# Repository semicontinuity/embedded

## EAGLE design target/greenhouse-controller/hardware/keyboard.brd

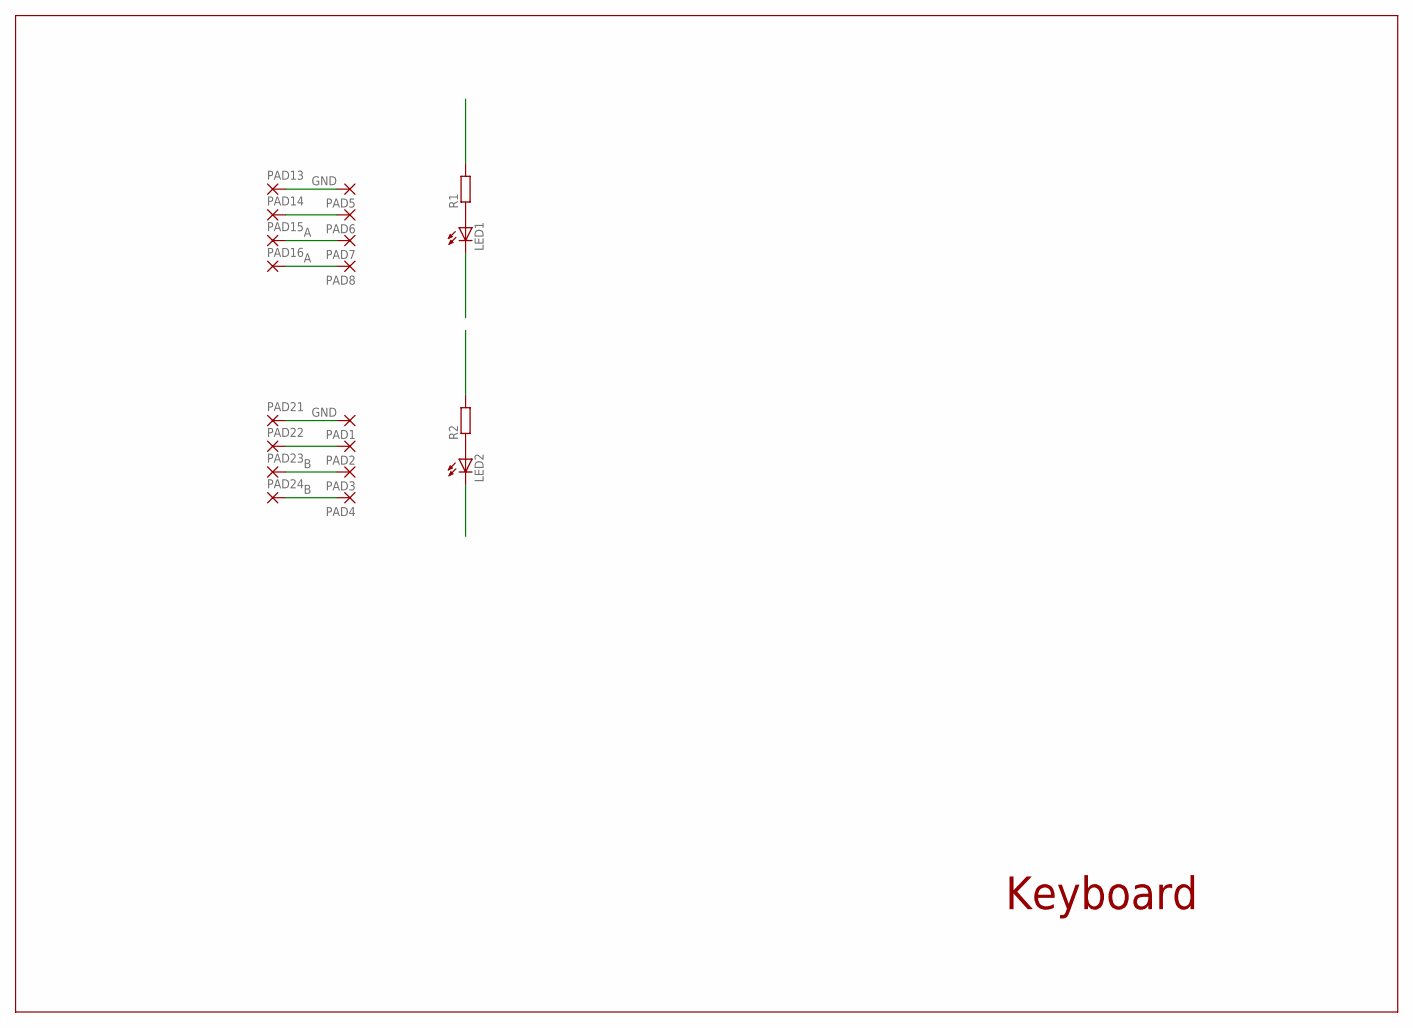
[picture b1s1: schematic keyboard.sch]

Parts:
LED1, LED2: LEDCHIP-LED0805; CHIP-LED0805
PAD1, PAD2, PAD3, PAD4, PAD5, PAD6, PAD7, PAD8, PAD13, PAD14, PAD15, PAD16, PAD21, PAD22, PAD23, PAD24: WIREPAD1,6/0,8; 1,6/0,8
R1, R2: R-EU_R0805; R0805

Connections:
A: PAD7.1, PAD8.1, PAD15.1, PAD16.1, R1.2
B: PAD3.1, PAD4.1, PAD23.1, PAD24.1, R2.2
GND: LED1.C, LED2.C, PAD1.1, PAD2.1, PAD5.1, PAD6.1, PAD13.1, PAD14.1, PAD21.1, PAD22.1
unnamed: LED1.A, R1.1
unnamed: LED2.A, R2.1

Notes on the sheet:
Keyboard

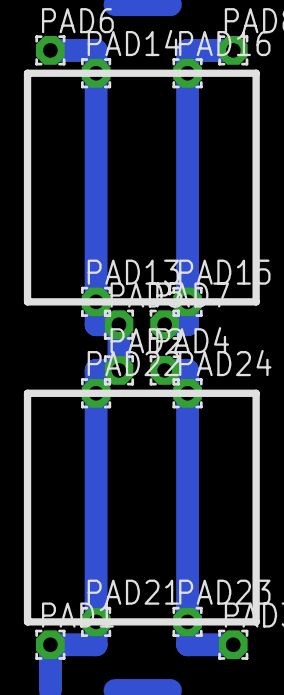
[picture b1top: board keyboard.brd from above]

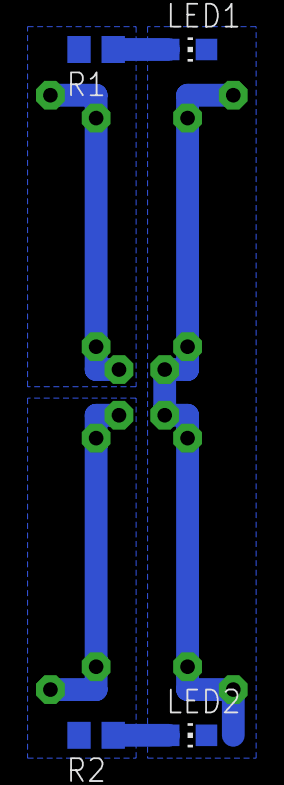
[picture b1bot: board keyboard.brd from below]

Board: 2 copper layers, 20 parts (4 on the bottom side), 5 nets.

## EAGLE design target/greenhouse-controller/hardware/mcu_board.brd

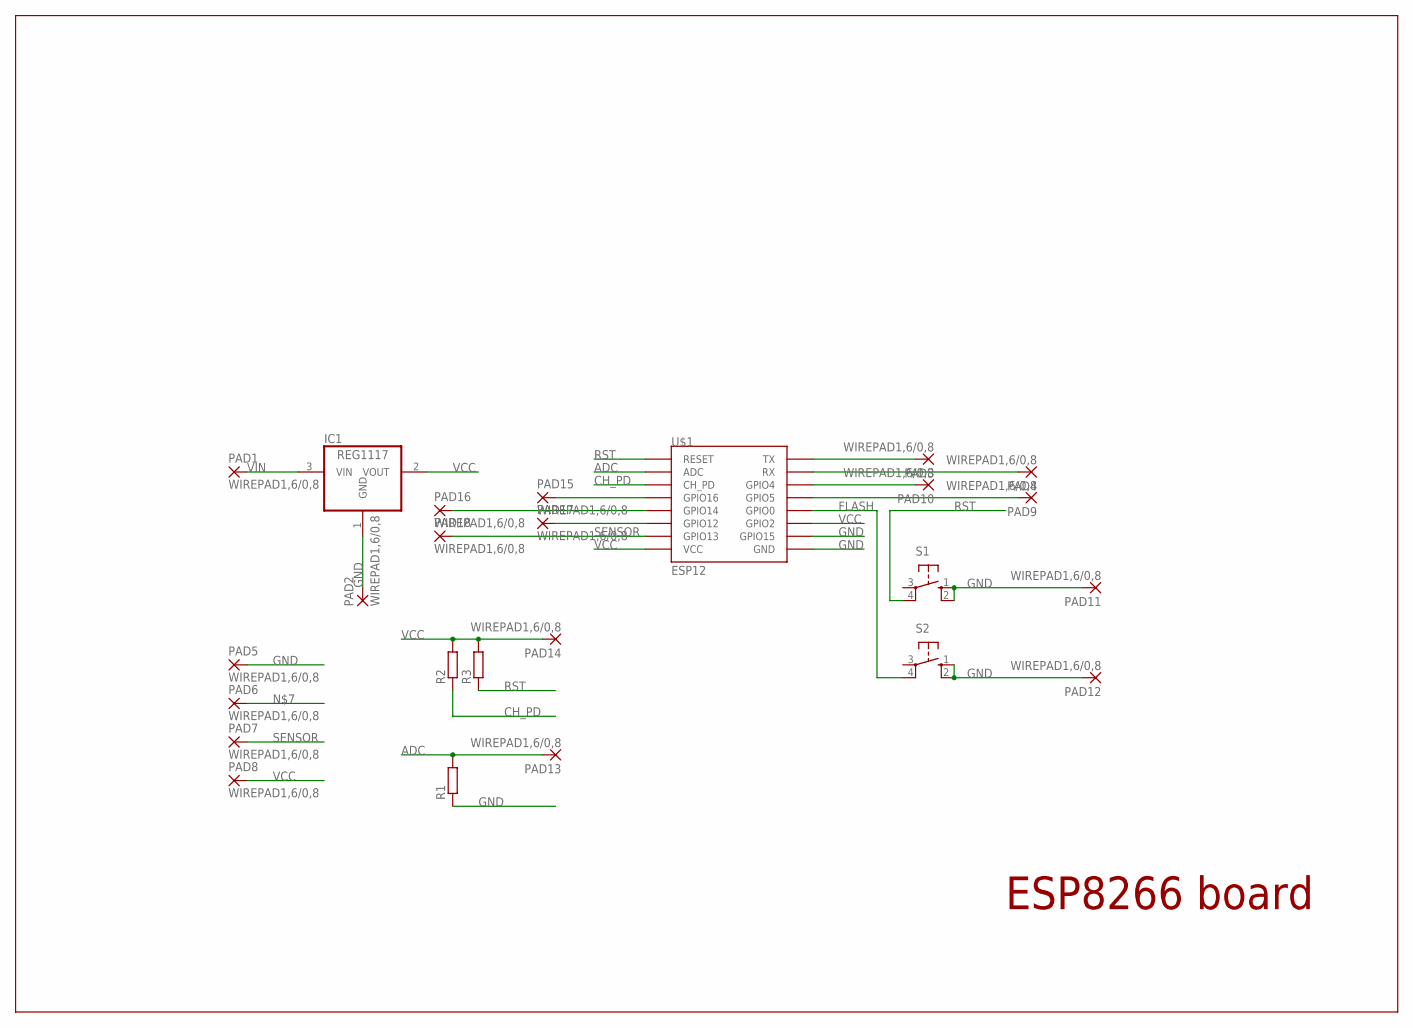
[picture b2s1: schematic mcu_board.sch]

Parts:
IC1: REG1117; SOT223
PAD1, PAD2, PAD3, PAD4, PAD5, PAD6, PAD7, PAD8, PAD9, PAD10, PAD11, PAD12, PAD13, PAD14, PAD15, PAD16, PAD17, PAD18: WIREPAD1,6/0,8; 1,6/0,8
R1, R2, R3: R-EU_M0805; M0805
S1, S2: 10-XX; B3F-10XX
U$1: ESP12

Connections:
ADC: PAD13.1, R1.2, U$1.ADC
CH_PD: R2.1, U$1.CH_PD
FLASH: S2.4 (P1), U$1.GPIO0
GND: IC1.1 (GND), PAD2.1, PAD5.1, PAD11.1, PAD12.1, R1.1, S1.1 (S), S1.2 (S1), S2.1 (S), S2.2 (S1), U$1.GND, U$1.GPIO15
unnamed: PAD3.1, U$1.TX
unnamed: PAD4.1, U$1.RX
unnamed: PAD10.1, U$1.GPIO4
unnamed: PAD9.1, U$1.GPIO5
unnamed: PAD15.1, U$1.GPIO16
unnamed: PAD16.1, U$1.GPIO14
unnamed: PAD17.1, U$1.GPIO12
RST: R3.1, S1.4 (P1), U$1.RESET
SENSOR: PAD7.1, PAD18.1, U$1.GPIO13
VCC: IC1.2 (VOUT), PAD8.1, PAD14.1, R2.2, R3.2, U$1.GPIO2, U$1.VCC
VIN: IC1.3 (VIN), PAD1.1

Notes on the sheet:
ESP8266 board

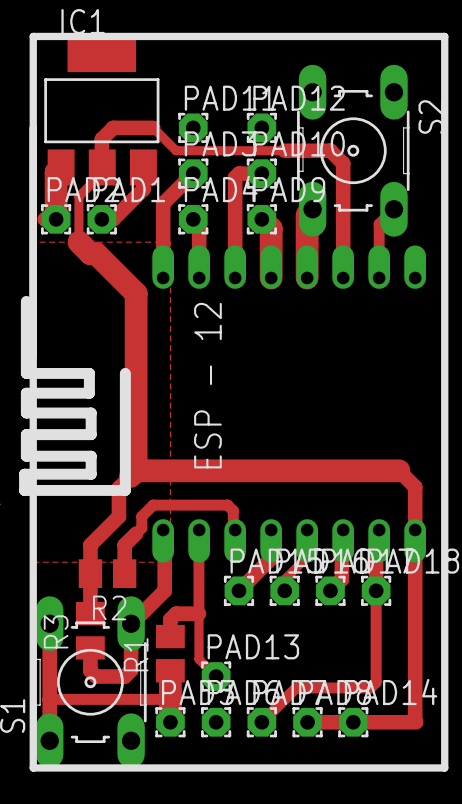
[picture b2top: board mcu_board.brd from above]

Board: 2 copper layers, 25 parts (0 on the bottom side), 15 nets.

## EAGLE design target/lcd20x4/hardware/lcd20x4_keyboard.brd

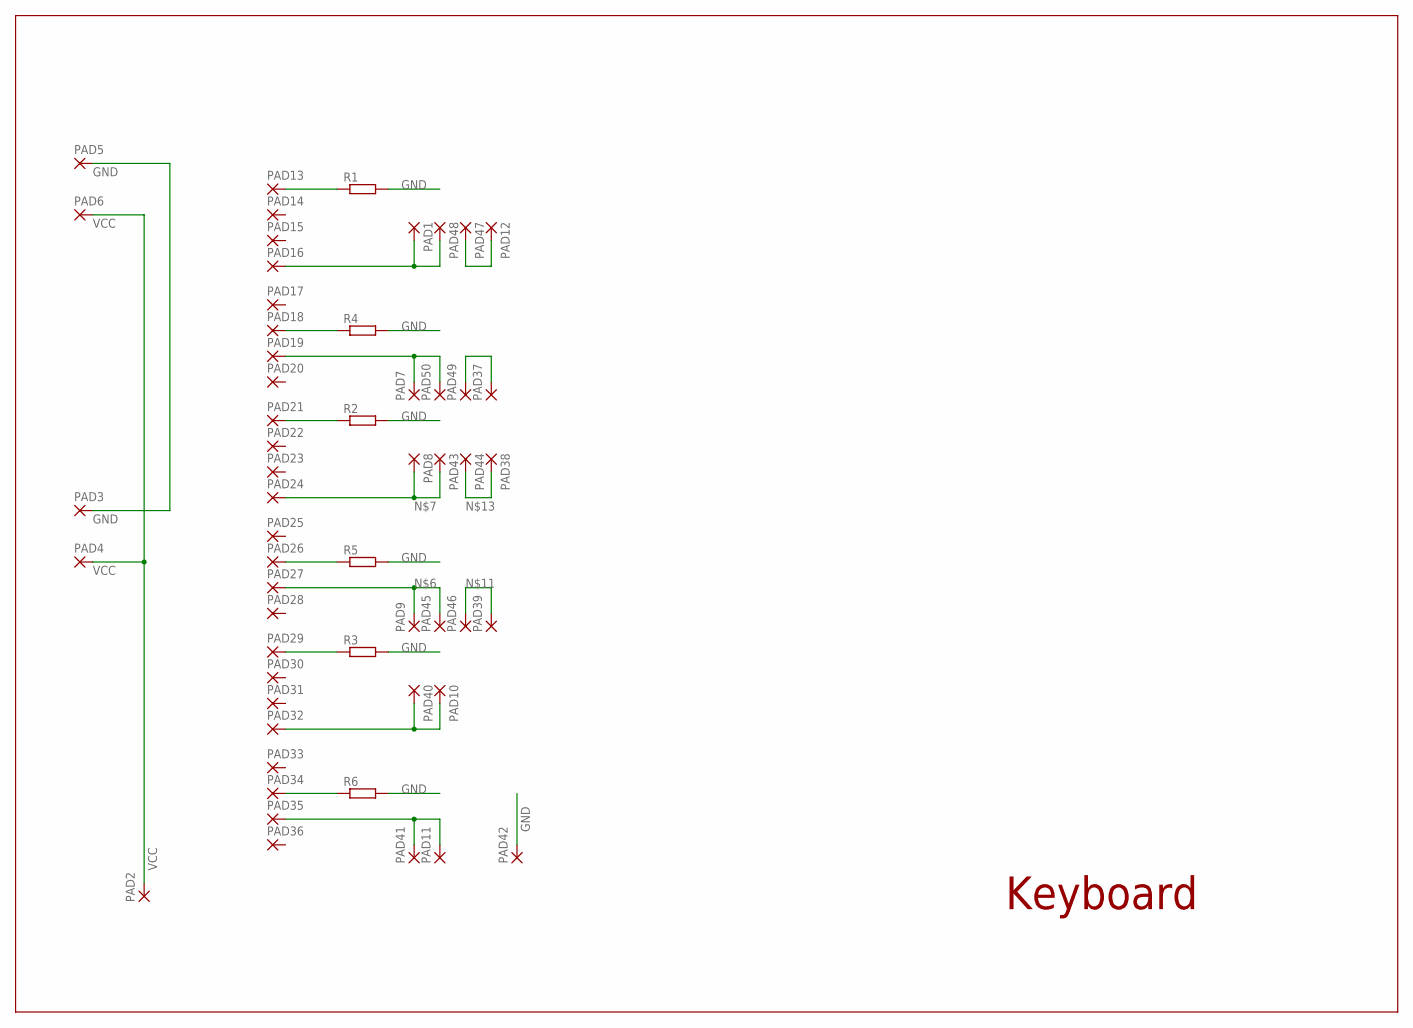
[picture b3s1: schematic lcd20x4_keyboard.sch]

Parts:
PAD1, PAD2, PAD3, PAD4, PAD5, PAD6, PAD7, PAD8, PAD9, PAD10, PAD11, PAD12, PAD13, PAD14, PAD15, PAD16, PAD17, PAD18, PAD19, PAD20, PAD21, PAD22, PAD23, PAD24, PAD25, PAD26, PAD27, PAD28, PAD29, PAD30, PAD31, PAD32, PAD33, PAD34, PAD35, PAD36, PAD37, PAD38, PAD39, PAD40, PAD41, PAD42, PAD43, PAD44, PAD45, PAD46, PAD47, PAD48, PAD49, PAD50: WIREPAD1,6/0,8; 1,6/0,8
R1, R2, R3, R4, R5, R6: R-EU_M0805; M0805

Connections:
GND: PAD3.1, PAD5.1, PAD42.1, R1.2, R2.2, R3.2, R4.2, R5.2, R6.2
unnamed: PAD29.1, R3.1
unnamed: PAD21.1, R2.1
unnamed: PAD13.1, R1.1
unnamed: PAD10.1, PAD32.1, PAD40.1
unnamed: PAD11.1, PAD35.1, PAD41.1
unnamed: PAD9.1, PAD27.1, PAD45.1
unnamed: PAD8.1, PAD24.1, PAD43.1
unnamed: PAD1.1, PAD16.1, PAD48.1
unnamed: PAD7.1, PAD19.1, PAD50.1
unnamed: PAD34.1, R6.1
unnamed: PAD39.1, PAD46.1
unnamed: PAD26.1, R5.1
unnamed: PAD38.1, PAD44.1
unnamed: PAD18.1, R4.1
unnamed: PAD37.1, PAD49.1
unnamed: PAD12.1, PAD47.1
VCC: PAD2.1, PAD4.1, PAD6.1

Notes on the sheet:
Keyboard

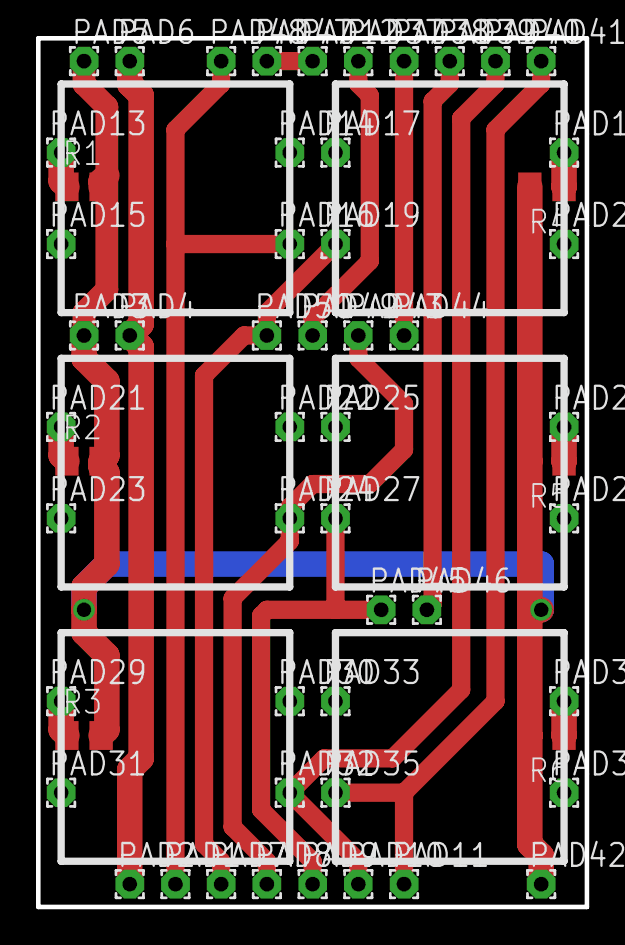
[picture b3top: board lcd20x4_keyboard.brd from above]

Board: 2 copper layers, 30.5 x 48.3 mm, 56 parts (0 on the bottom side), 18 nets.

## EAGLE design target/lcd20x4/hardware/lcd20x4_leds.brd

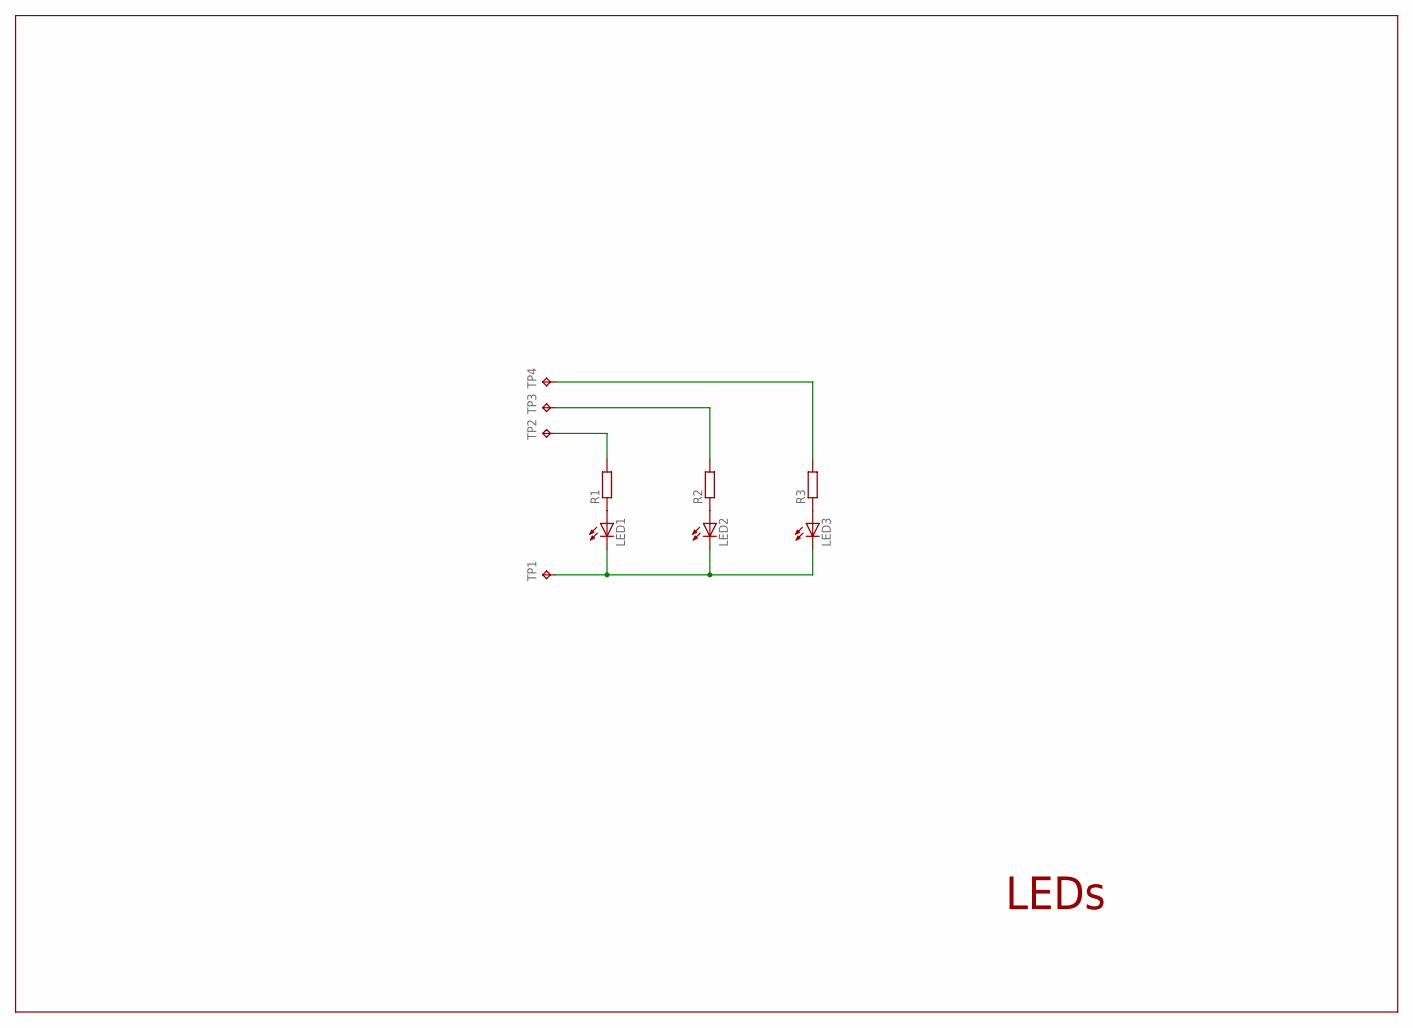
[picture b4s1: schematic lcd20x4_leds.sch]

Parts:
LED1, LED2, LED3: LED5MM
R1, R2, R3: R-EU_R0805; R0805
TP1, TP2, TP3, TP4: TPB1,27; B1,27

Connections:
GND: LED1.K (C), LED2.K (C), LED3.K (C), TP1.TP
unnamed: LED1.A, R1.1
unnamed: LED2.A, R2.1
unnamed: LED3.A, R3.1
unnamed: R1.2, TP2.TP
unnamed: R2.2, TP3.TP
unnamed: R3.2, TP4.TP

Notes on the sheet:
LEDs

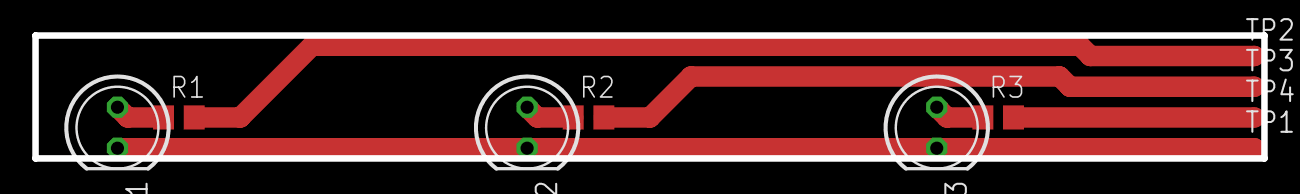
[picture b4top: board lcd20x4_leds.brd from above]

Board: 2 copper layers, 76.2 x 7.6 mm, 10 parts (0 on the bottom side), 7 nets.

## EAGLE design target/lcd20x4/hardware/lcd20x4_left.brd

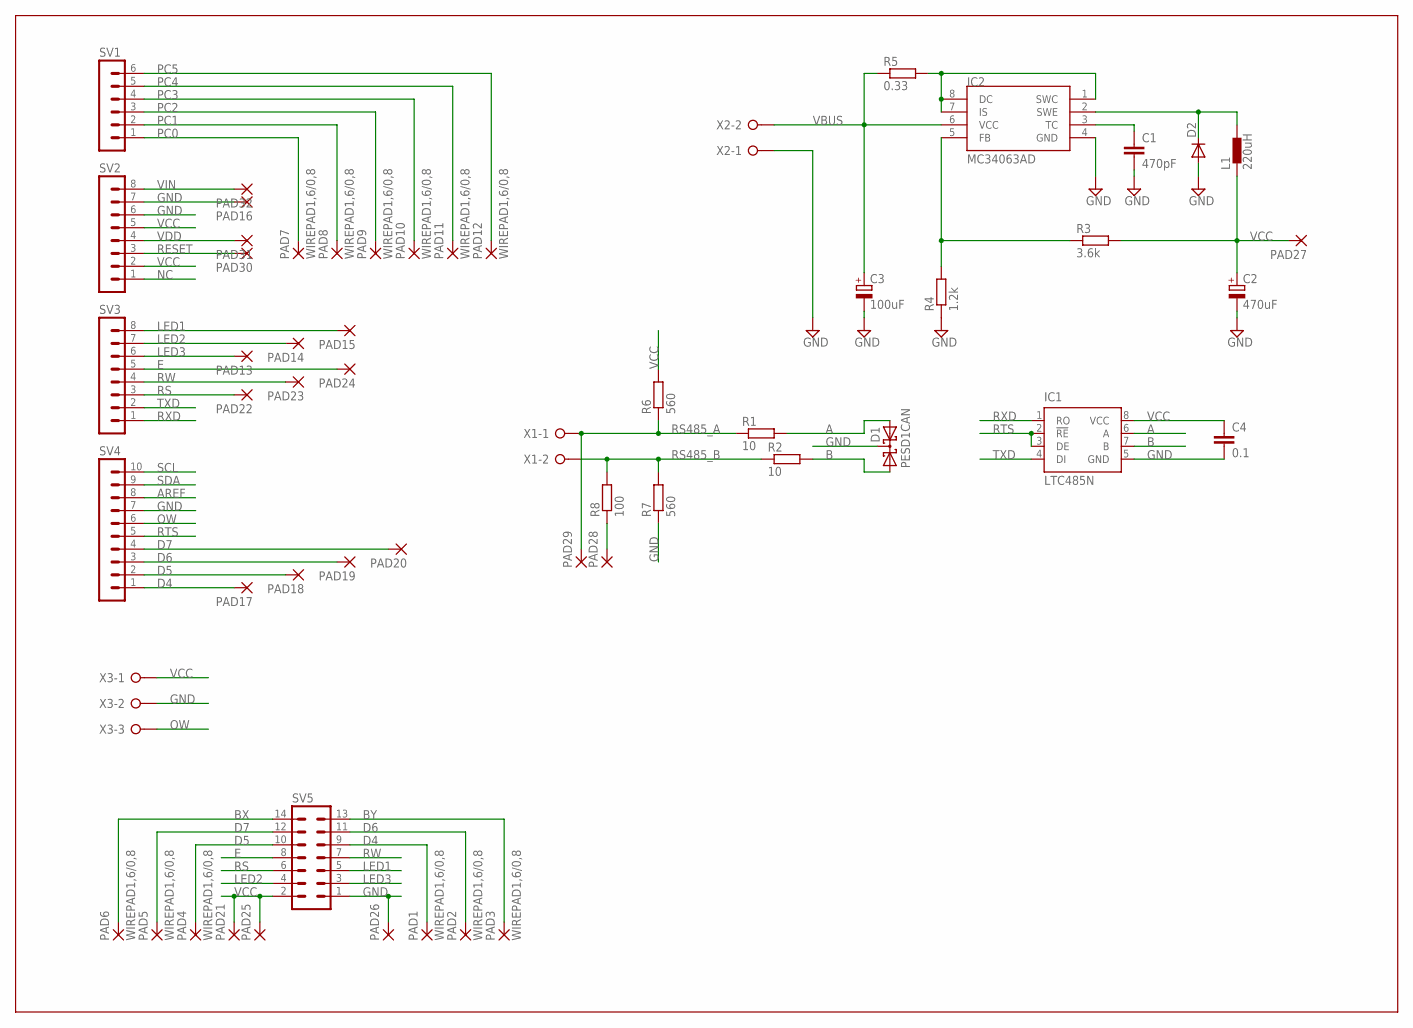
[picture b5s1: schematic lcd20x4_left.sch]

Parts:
C1: 470pF; C0805
C2: 470uF; E3,5-8
C3: 100uF; E3,5-8
C4: 0.1; C0805
D1: PESD1CAN; SOT23
D2: DIODE-SMB; SMB
IC1: LTC485N; DIL08
IC2: MC34063AD; SOIC8
L1: 220uH; DR1030
PAD1, PAD2, PAD3, PAD4, PAD5, PAD6, PAD7, PAD8, PAD9, PAD10, PAD11, PAD12, PAD13, PAD14, PAD15, PAD16, PAD17, PAD18, PAD19, PAD20, PAD21, PAD22, PAD23, PAD24, PAD25, PAD26, PAD27, PAD28, PAD29, PAD30, PAD31, PAD32: WIREPAD1,6/0,8; 1,6/0,8
R1, R2: 10; 0207/10
R3: 3.6k; R0805
R4: 1.2k; R0805
R5: 0.33; M1206
R6, R7: 560; 0207/10
R8: 100; 0207/10
SV1: MA06-1
SV2, SV3: MA08-1
SV4: MA10-1
SV5: MA07-2
X1, X2: W237-02P; W237-132
X3: W237-03P; W237-133

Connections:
A: D1.2 (A2), IC1.6 (A), R1.2
AREF: SV4.8
B: D1.1 (A1), IC1.7 (B), R2.2
BX: PAD6.1, SV5.14
BY: PAD3.1, SV5.13
D4: PAD1.1, PAD17.1, SV4.1, SV5.9
D5: PAD4.1, PAD18.1, SV4.2, SV5.10
D6: PAD2.1, PAD19.1, SV4.3, SV5.11
D7: PAD5.1, PAD20.1, SV4.4, SV5.12
E: PAD24.1, SV3.5, SV5.8
GND: C1.2, C2.-, C3.-, C4.2, D1.3 (CC), D2.A, IC1.5 (GND), IC2.4 (GND), PAD16.1, PAD26.1, R4.1, R7.1, SV2.6, SV2.7, SV4.7, SV5.1, X2.1, X3.2
LED1: PAD15.1, SV3.8, SV5.5
LED2: PAD14.1, SV3.7, SV5.4
LED3: PAD13.1, SV3.6, SV5.3
unnamed: C1.1, IC2.3 (TC)
unnamed: D2.C, IC2.2 (SWE), L1.2
unnamed: IC2.1 (SWC), IC2.7 (IS), IC2.8 (DC), R5.2
unnamed: IC2.5 (FB), R3.1, R4.2
unnamed: PAD28.1, R8.1
NC: SV2.1
OW: SV4.6, X3.3
PC0: PAD7.1, SV1.1
PC1: PAD8.1, SV1.2
PC2: PAD9.1, SV1.3
PC3: PAD10.1, SV1.4
PC4: PAD11.1, SV1.5
PC5: PAD12.1, SV1.6
RESET: PAD30.1, SV2.3
RS: PAD22.1, SV3.3, SV5.6
RS485_A: PAD29.1, R1.1, R6.1, X1.1
RS485_B: R2.1, R7.2, R8.2, X1.2
RTS: IC1.2 (!RE), IC1.3 (DE), SV4.5
RW: PAD23.1, SV3.4, SV5.7
RXD: IC1.1 (RO), SV3.1
SCL: SV4.10
SDA: SV4.9
TXD: IC1.4 (DI), SV3.2
VBUS: C3.+, IC2.6 (VCC), R5.1, X2.2
VCC: C2.+, C4.1, IC1.8 (VCC), L1.1, PAD21.1, PAD25.1, PAD27.1, R3.2, R6.2, SV2.2, SV2.5, SV5.2, X3.1
VDD: PAD31.1, SV2.4
VIN: PAD32.1, SV2.8

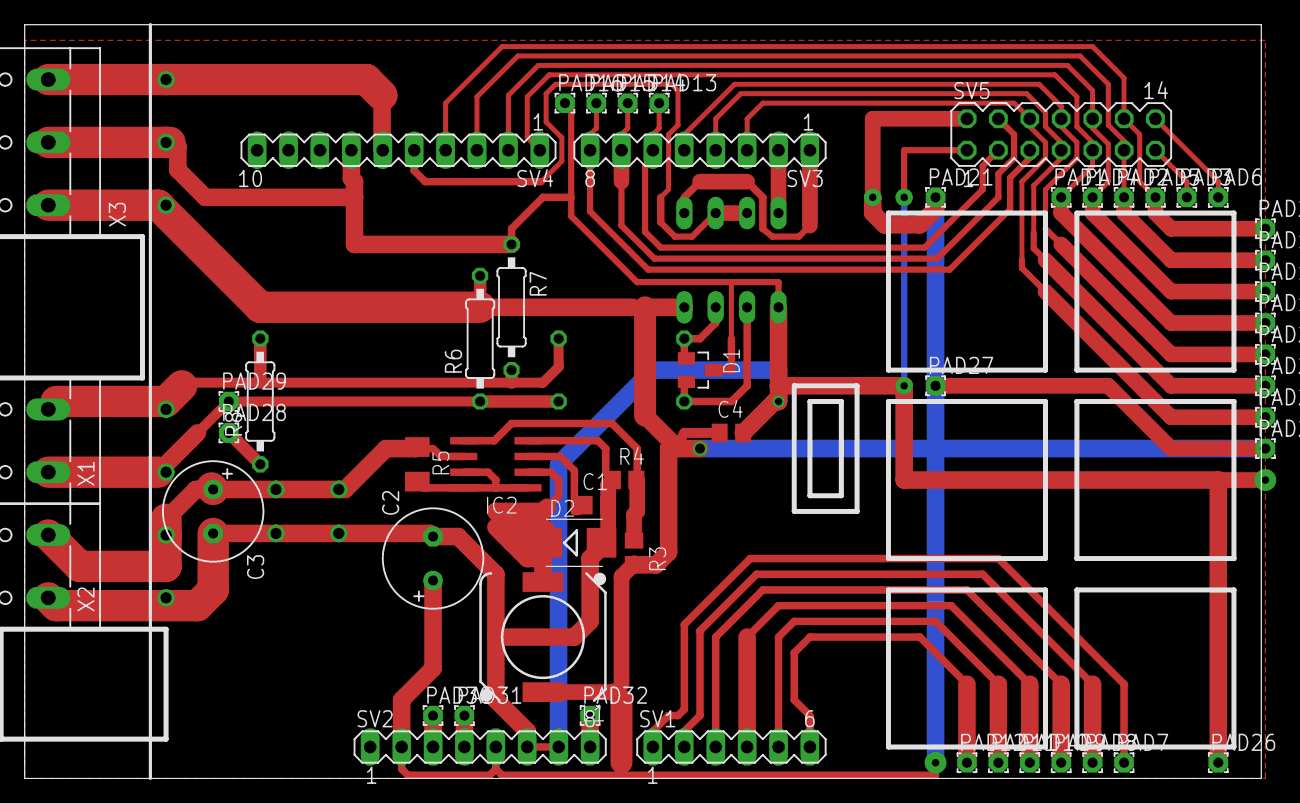
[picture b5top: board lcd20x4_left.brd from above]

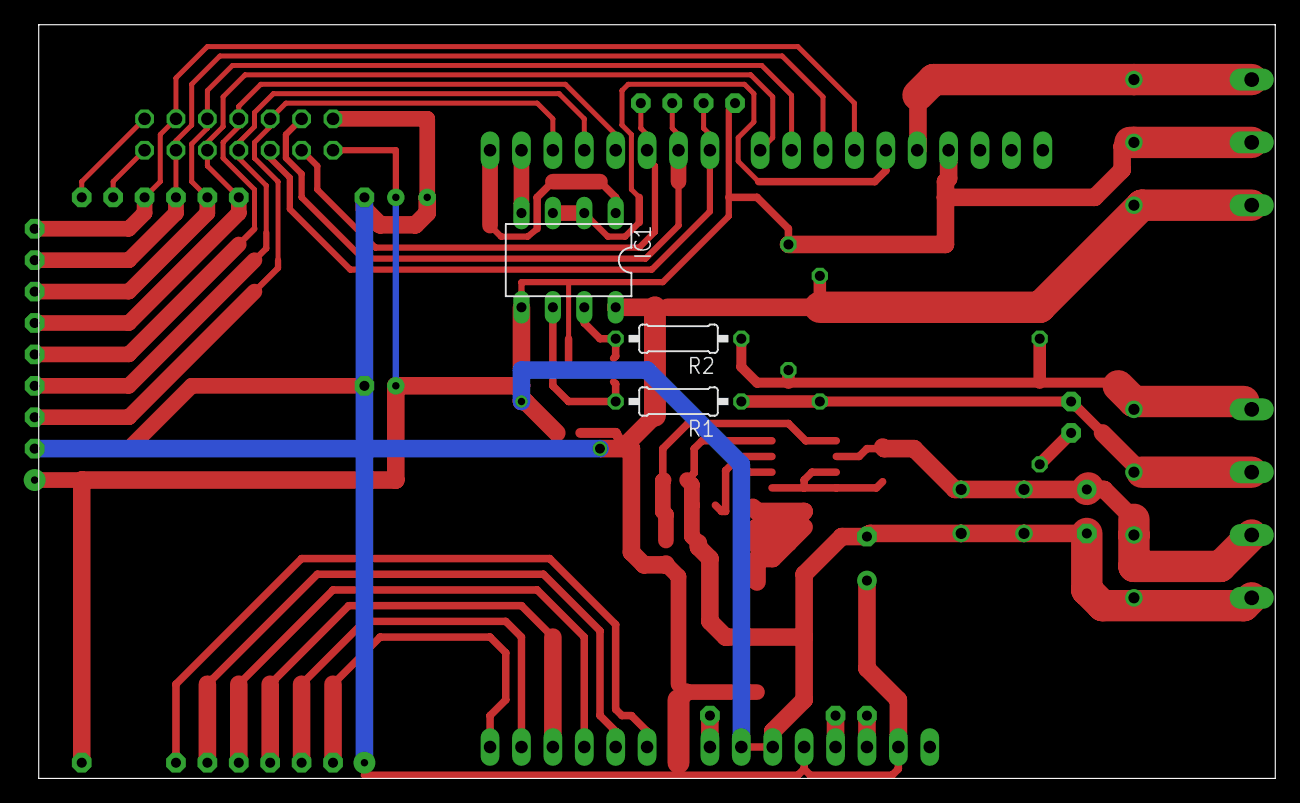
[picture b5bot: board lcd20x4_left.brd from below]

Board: 2 copper layers, 100.0 x 61.0 mm, 57 parts (3 on the bottom side), 37 nets.

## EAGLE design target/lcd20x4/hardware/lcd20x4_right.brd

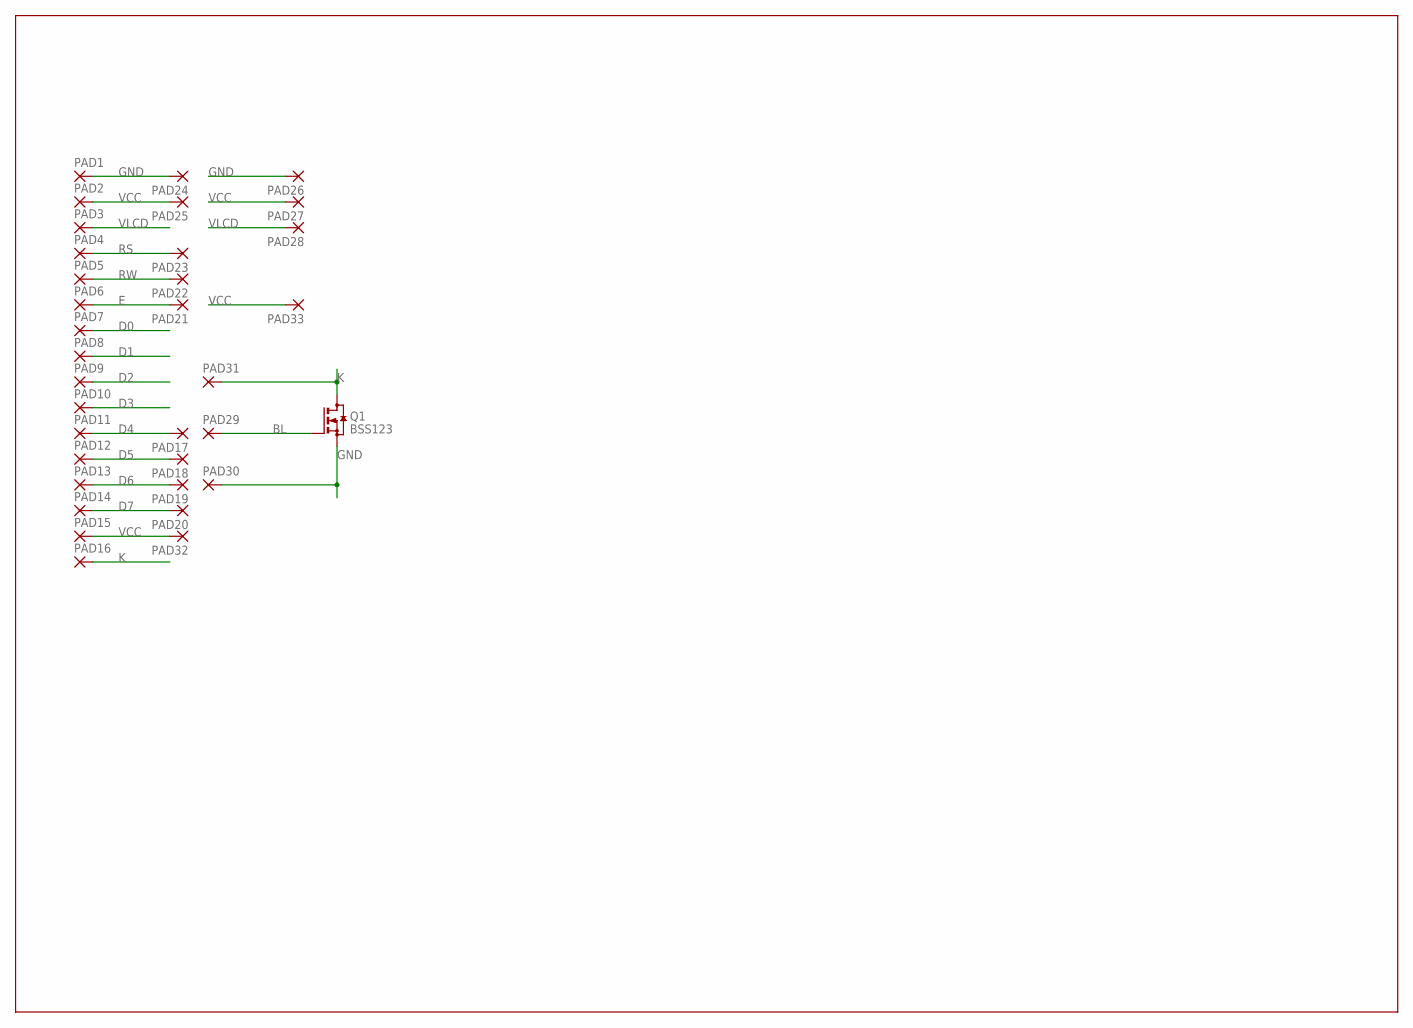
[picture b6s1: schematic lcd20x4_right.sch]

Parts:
PAD1, PAD2, PAD3, PAD4, PAD5, PAD6, PAD7, PAD8, PAD9, PAD10, PAD11, PAD12, PAD13, PAD14, PAD15, PAD16, PAD17, PAD18, PAD19, PAD20, PAD21, PAD22, PAD23, PAD24, PAD25, PAD26, PAD27, PAD28, PAD29, PAD30, PAD31, PAD32, PAD33: WIREPAD1,6/0,8; 1,6/0,8
Q1: BSS123; SOT23

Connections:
BL: PAD29.1, Q1.1 (G)
D0: PAD7.1
D1: PAD8.1
D2: PAD9.1
D3: PAD10.1
D4: PAD11.1, PAD17.1
D5: PAD12.1, PAD18.1
D6: PAD13.1, PAD19.1
D7: PAD14.1, PAD20.1
E: PAD6.1, PAD21.1
GND: PAD1.1, PAD24.1, PAD26.1, PAD30.1, Q1.2 (S)
K: PAD16.1, PAD31.1, Q1.3 (D)
RS: PAD4.1, PAD23.1
RW: PAD5.1, PAD22.1
VCC: PAD2.1, PAD15.1, PAD25.1, PAD27.1, PAD32.1, PAD33.1
VLCD: PAD3.1, PAD28.1

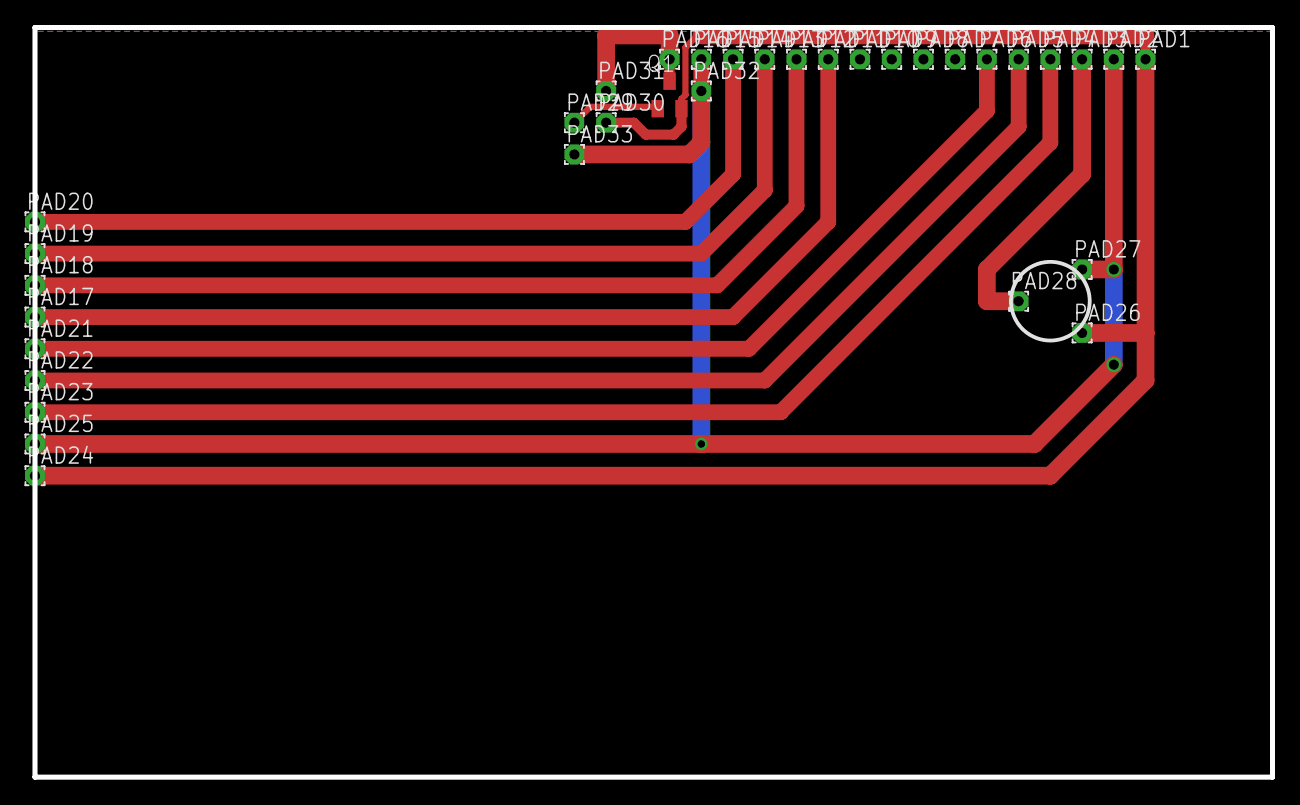
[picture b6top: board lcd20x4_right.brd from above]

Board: 2 copper layers, 99.1 x 60.0 mm, 34 parts (0 on the bottom side), 12 nets.

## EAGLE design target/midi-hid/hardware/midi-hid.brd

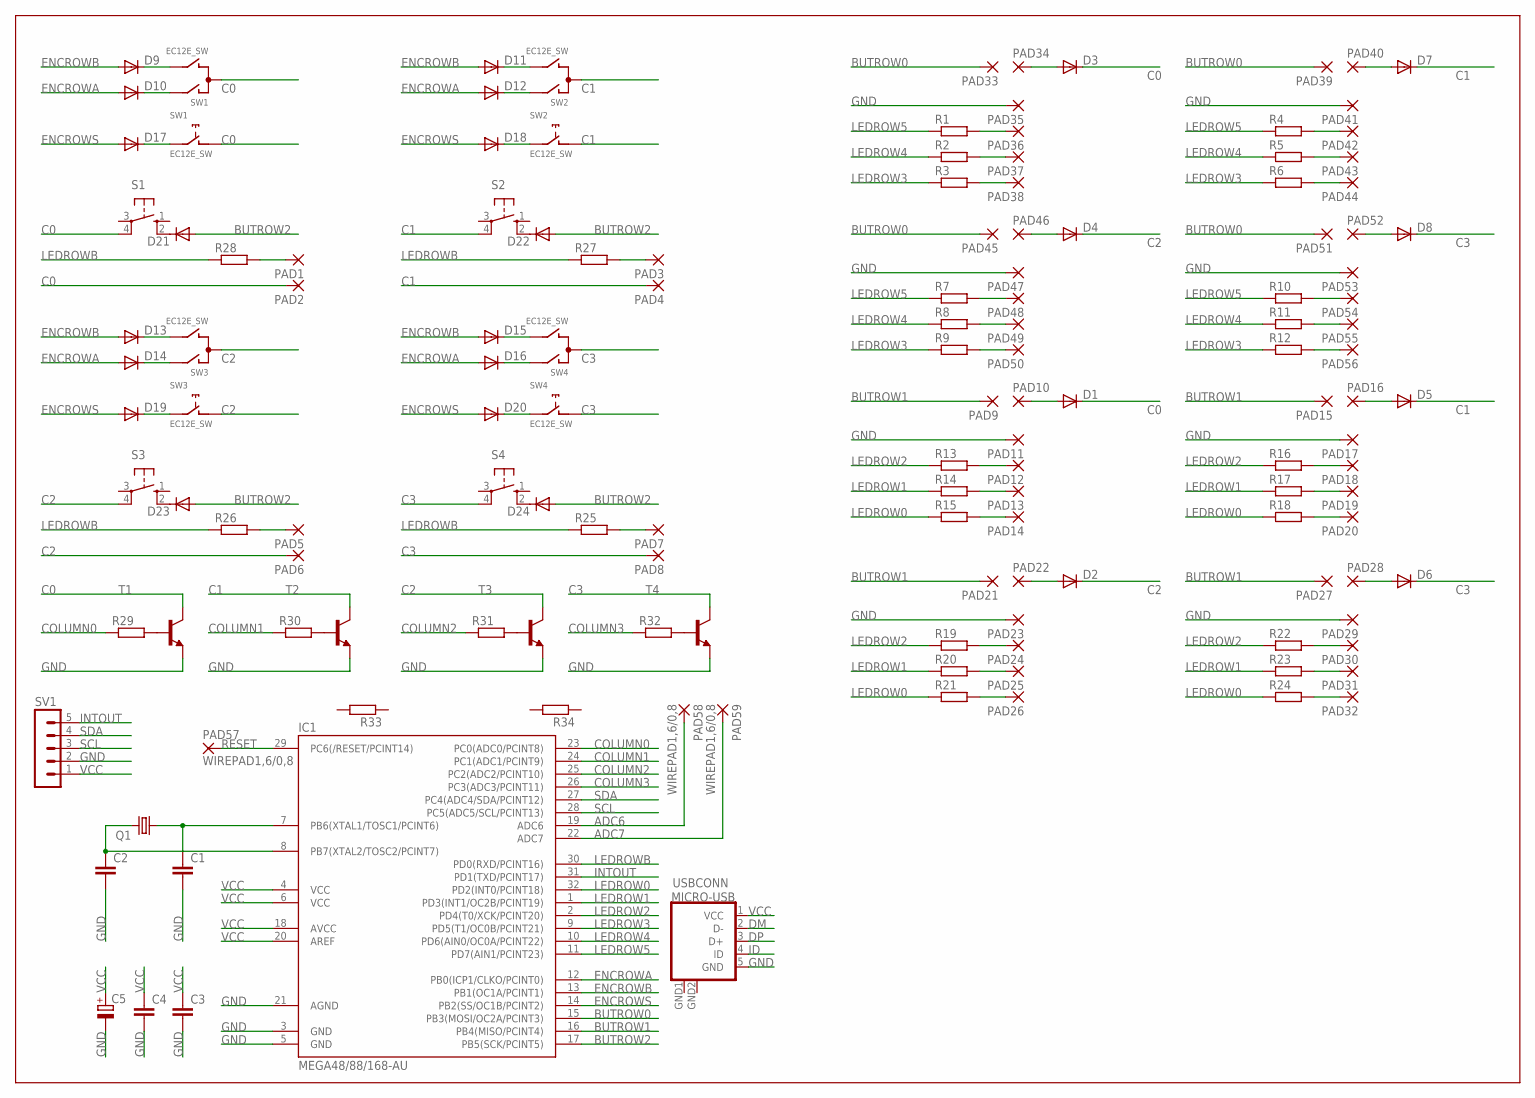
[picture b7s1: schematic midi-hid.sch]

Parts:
C1, C2, C3, C4: C-EUC0805; C0805
C5: CPOL-EUE2.5-6; E2,5-6
D1, D2, D3, D4, D5, D6, D7, D8, D9, D10, D11, D12, D13, D14, D15, D16, D17, D18, D19, D20, D21, D22, D23, D24: DIODE-SOD80C; SOD80C
IC1: MEGA48/88/168-AU; TQFP32-08
PAD1, PAD2, PAD3, PAD4, PAD5, PAD6, PAD7, PAD8, PAD9, PAD10, PAD11, PAD12, PAD13, PAD14, PAD15, PAD16, PAD17, PAD18, PAD19, PAD20, PAD21, PAD22, PAD23, PAD24, PAD25, PAD26, PAD27, PAD28, PAD29, PAD30, PAD31, PAD32, PAD33, PAD34, PAD35, PAD36, PAD37, PAD38, PAD39, PAD40, PAD41, PAD42, PAD43, PAD44, PAD45, PAD46, PAD47, PAD48, PAD49, PAD50, PAD51, PAD52, PAD53, PAD54, PAD55, PAD56: 1,6/0,8
PAD57, PAD58, PAD59: WIREPAD1,6/0,8; 1,6/0,8
Q1: CRYSTALHC49S; HC49/S
R1, R2, R3, R4, R5, R6, R7, R8, R9, R10, R11, R12, R13, R14, R15, R16, R17, R18, R19, R20, R21, R22, R23, R24, R25, R26, R27, R28, R29, R30, R31, R32: R-EU_R0805; R0805
R33, R34: R-EU_0207/10; 0207/10
S1, S2, S3, S4: 40-XX; B3F-40XX
SV1: MA05-1
SW1, SW2, SW3, SW4: EC12E_SW; ALPS_EC12E_SW
T1, T2, T3, T4: MMBT3904LT1-NPN-SOT23-BEC; SOT23-BEC
USBCONN: MICRO-USB

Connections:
ADC6: IC1.19 (ADC6), PAD58.1
ADC7: IC1.22 (ADC7), PAD59.1
BUTROW0: IC1.15 (PB3(MOSI/OC2A/PCINT3)), PAD33.1, PAD39.1, PAD45.1, PAD51.1
BUTROW1: IC1.16 (PB4(MISO/PCINT4)), PAD9.1, PAD15.1, PAD21.1, PAD27.1
BUTROW2: D21.A, D22.A, D23.A, D24.A, IC1.17 (PB5(SCK/PCINT5))
C0: D1.C, D3.C, PAD2.1, S1.4 (P1), SW1.C, SW1.D (1), T1.C
C1: D5.C, D7.C, PAD4.1, S2.4 (P1), SW2.C, SW2.D (1), T2.C
C2: D2.C, D4.C, PAD6.1, S3.4 (P1), SW3.C, SW3.D (1), T3.C
C3: D6.C, D8.C, PAD8.1, S4.4 (P1), SW4.C, SW4.D (1), T4.C
COLUMN0: IC1.23 (PC0(ADC0/PCINT8)), R29.1
COLUMN1: IC1.24 (PC1(ADC1/PCINT9)), R30.1
COLUMN2: IC1.25 (PC2(ADC2/PCINT10)), R31.1
COLUMN3: IC1.26 (PC3(ADC3/PCINT11)), R32.1
DM: USBCONN.2 (D-); also elsewhere on the board
DP: USBCONN.3 (D+); also elsewhere on the board
ENCROWA: D10.A, D12.A, D14.A, D16.A, IC1.12 (PB0(ICP1/CLKO/PCINT0))
ENCROWB: D9.A, D11.A, D13.A, D15.A, IC1.13 (PB1(OC1A/PCINT1))
ENCROWS: D17.A, D18.A, D19.A, D20.A, IC1.14 (PB2(SS/OC1B/PCINT2))
GND: C1.2, C2.2, C3.2, C4.2, C5.-, IC1.3 (GND), IC1.5 (GND), IC1.21 (AGND), PAD11.1, PAD17.1, PAD23.1, PAD29.1, PAD35.1, PAD41.1, PAD47.1, PAD53.1, SV1.2, T1.E, T2.E, T3.E, T4.E, USBCONN.5 (GND), USBCONN.GND1 (GND), USBCONN.GND2 (GND); also elsewhere on the board
ID: USBCONN.4 (ID)
INTOUT: IC1.31 (PD1(TXD/PCINT17)), SV1.5
LEDROW2: IC1.2 (PD4(T0/XCK/PCINT20)), R13.1, R16.1, R19.1, R22.1
LEDROW3: IC1.9 (PD5(T1/OC0B/PCINT21)), R3.1, R6.1, R9.1, R12.1
LEDROW4: IC1.10 (PD6(AIN0/OC0A/PCINT22)), R2.1, R5.1, R8.1, R11.1
LEDROW5: IC1.11 (PD7(AIN1/PCINT23)), R1.1, R4.1, R7.1, R10.1
LEDROWB: IC1.30 (PD0(RXD/PCINT16)), R25.1, R26.1, R27.1, R28.1
unnamed: D9.C, SW1.B
unnamed: D10.C, SW1.A
unnamed: D17.C, SW1.E (2)
unnamed: D11.C, SW2.B
unnamed: D12.C, SW2.A
unnamed: D18.C, SW2.E (2)
unnamed: D13.C, SW3.B
unnamed: D14.C, SW3.A
unnamed: D19.C, SW3.E (2)
unnamed: D15.C, SW4.B
unnamed: D16.C, SW4.A
unnamed: D20.C, SW4.E (2)
unnamed: C1.1, IC1.7 (PB6(XTAL1/TOSC1/PCINT6)), Q1.1
unnamed: C2.1, IC1.8 (PB7(XTAL2/TOSC2/PCINT7)), Q1.2
unnamed: R29.2, T1.B
unnamed: PAD36.1, R1.2
unnamed: PAD37.1, R2.2
unnamed: PAD38.1, R3.2
unnamed: R30.2, T2.B
unnamed: PAD42.1, R4.2
unnamed: PAD43.1, R5.2
unnamed: PAD44.1, R6.2
unnamed: R31.2, T3.B
unnamed: PAD48.1, R7.2
unnamed: PAD49.1, R8.2
unnamed: PAD50.1, R9.2
unnamed: R32.2, T4.B
unnamed: PAD54.1, R10.2
unnamed: PAD55.1, R11.2
unnamed: PAD56.1, R12.2
unnamed: D3.A, PAD34.1
unnamed: D7.A, PAD40.1
unnamed: D4.A, PAD46.1
unnamed: D8.A, PAD52.1
unnamed: PAD14.1, R15.2
unnamed: PAD13.1, R14.2
unnamed: PAD12.1, R13.2
unnamed: PAD20.1, R18.2
unnamed: PAD19.1, R17.2
unnamed: PAD18.1, R16.2
unnamed: PAD24.1, R19.2
unnamed: PAD25.1, R20.2
unnamed: PAD26.1, R21.2
unnamed: PAD32.1, R24.2
unnamed: PAD31.1, R23.2
unnamed: PAD30.1, R22.2
unnamed: D1.A, PAD10.1
unnamed: D5.A, PAD16.1
unnamed: D2.A, PAD22.1
unnamed: D6.A, PAD28.1
unnamed: PAD1.1, R28.2
unnamed: PAD3.1, R27.2
unnamed: PAD5.1, R26.2
unnamed: PAD7.1, R25.2
unnamed: D22.C, S2.2 (S1)
unnamed: D21.C, S1.2 (S1)
unnamed: D23.C, S3.2 (S1)
unnamed: D24.C, S4.2 (S1)
RESET: IC1.29 (PC6(/RESET/PCINT14)), PAD57.1
SCL: IC1.28 (PC5(ADC5/SCL/PCINT13)), SV1.3; also elsewhere on the board
SDA: IC1.27 (PC4(ADC4/SDA/PCINT12)), SV1.4; also elsewhere on the board
VCC: C3.1, C4.1, C5.+, IC1.4 (VCC), IC1.6 (VCC), IC1.18 (AVCC), IC1.20 (AREF), SV1.1, USBCONN.1 (VCC); also elsewhere on the board

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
